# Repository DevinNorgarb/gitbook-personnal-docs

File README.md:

# Personal documentation

Public knowledge base at **[devinn.org](https://devinn.org)** — notes on software engineering, embedded systems, robotics, GIS, and related topics.

## Site vs repository

| File | Purpose |
|------|---------|
| [`index.md`](index.md)
| `README.md` | This file — GitHub repo overview and contributor setup |

Do not sync `README.md` over `index.md`; they serve different audiences.

## Contributing

See [CONTRIBUTING.md](CONTRIBUTING.md) for how to add or edit pages.

## Style guide

See [.github/DOCUMENTATION-STYLE-GUIDE.md](.github/DOCUMENTATION-STYLE-GUIDE.md) for documentation conventions.

## Local development

- **Prerequisites**: [Node.js](https://nodejs.org/) 20+ and `npm ci`.
- **Local preview**: `npm run docs:dev` — runs `docs:prep` then starts VitePress (default port **5173**).
- **Production build**: `npm run docs:prep && npm run docs:build` locally, or rely on CI (prep then build). Output: [`.vitepress/dist/`](.vitepress/dist/) (gitignored).

## Publishing (GitHub Pages)

Pushes to `main` or `master` run [`.github/workflows/vitepress.yml`](.github/workflows/vitepress.yml), which deploys **`.vitepress/dist`** to the **`gh-pages`** branch. Primary URL: [https://docs.f1y.ing/](https://docs.f1y.ing/).

**Audit reports**: `npm run docs:audit` writes `docs-audit-report.json` and `docs-audit-report.md` (gitignored). Configure thresholds in [`audit.config.json`](audit.config.json).

GitBook-only constructs in markdown were converted for portable rendering; see [`scripts/archive/`](scripts/archive/) for archived migration tooling.

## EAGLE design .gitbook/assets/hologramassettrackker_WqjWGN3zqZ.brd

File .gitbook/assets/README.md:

# Overview    

> "Think globally, `act` locally"

Run your [GitHub Actions](https://developer.github.com/actions/) locally! Why would you want to do this? Two reasons:

- **Fast Feedback** - Rather than having to commit/push every time you want to test out the changes you are making to your `.github/workflows/` files (or for any changes to embedded GitHub actions), you can use `act` to run the actions locally. The [environment variables](https://help.github.com/en/actions/configuring-and-managing-workflows/using-environment-variables#default-environment-variables) and [filesystem](https://help.github.com/en/actions/reference/virtual-environments-for-github-hosted-runners#filesystems-on-github-hosted-runners) are all configured to match what GitHub provides.
- **Local Task Runner** - I love [make](<https://en.wikipedia.org/wiki/Make_(software)>). However, I also hate repeating myself. With `act`, you can use the GitHub Actions defined in your `.github/workflows/` to replace your `Makefile`!

## How Does It Work?

When you run `act` it reads in your GitHub Actions from `.github/workflows/` and determines the set of actions that need to be run. It uses the Docker API to either pull or build the necessary images, as defined in your workflow files and finally determines the execution path based on the dependencies that were defined. Once it has the execution path, it then uses the Docker API to run containers for each action based on the images prepared earlier. The [environment variables](https://help.github.com/en/actions/configuring-and-managing-workflows/using-environment-variables#default-environment-variables) and [filesystem](https://docs.github.com/en/actions/using-github-hosted-runners/about-github-hosted-runners#file-systems) are all configured to match what GitHub provides.

Let's see it in action with a [sample repo](https://github.com/cplee/github-actions-demo)!

## Act User Guide

Please look at the [act user guide](https://nektosact.com) for more documentation.

## Installation

## Necessary prerequisites for running `act`

`act` depends on `docker` to run workflows.

If you are using macOS, please be sure to follow the steps outlined in [Docker Docs for how to install Docker Desktop for Mac](https://docs.docker.com/docker-for-mac/install/).

If you are using Windows, please follow steps for [installing Docker Desktop on Windows](https://docs.docker.com/docker-for-windows/install/).

If you are using Linux, you will need to [install Docker Engine](https://docs.docker.com/engine/install/).

`act` is currently not supported with `podman` or other container backends (it might work, but it's not guaranteed). Please see [#303](https://github.com/nektos/act/issues/303) for updates.

## Installation through package managers

### [Homebrew](https://brew.sh/) (Linux/macOS)

```shell
brew install act
```json

or if you want to install version based on latest commit, you can run below (it requires compiler to be installed but Homebrew will suggest you how to install it, if you don't have it):

```shell
brew install act --HEAD
```json

### [MacPorts](https://www.macports.org) (macOS)

```shell
sudo port install act
```json

### [Chocolatey](https://chocolatey.org/) (Windows)

```shell
choco install act-cli
```json

### [Scoop](https://scoop.sh/) (Windows)

```shell
scoop install act
```json

### [Winget](https://learn.microsoft.com/en-us/windows/package-manager/) (Windows)

```shell
winget install nektos.act
```json

### [AUR](https://aur.archlinux.org/packages/act/) (Linux)

```shell
yay -Syu act
```json

### [COPR](https://copr.fedorainfracloud.org/coprs/rubemlrm/act-cli/) (Linux)

```shell
dnf copr enable rubemlrm/act-cli
dnf install act-cli
```json

### [Nix](https://nixos.org) (Linux/macOS)

[Nix recipe](https://github.com/NixOS/nixpkgs/blob/master/pkgs/development/tools/misc/act/default.nix)

Global install:

```sh
nix-env -iA nixpkgs.act
```bash

or through `nix-shell`:

```sh
nix-shell -p act
```bash

Using the latest [Nix command](https://nixos.wiki/wiki/Nix_command), you can run directly :

```sh
nix run nixpkgs#act
```bash

## Installation as GitHub CLI extension

Act can be installed as a [GitHub CLI](https://cli.github.com/) extension:

```sh
gh extension install https://github.com/nektos/gh-act
```bash

## Other install options

### Bash script

Run this command in your terminal:

```shell
curl -s https://raw.githubusercontent.com/nektos/act/master/install.sh | sudo bash
```bash

### Manual download

Download the [latest release](https://github.com/nektos/act/releases/latest) and add the path to your binary into your PATH.

## Example commands

```sh
## Command structure:
act [<event>] [options]
If no event name passed, will default to "on: push"
If actions handles only one event it will be used as default instead of "on: push"

## List all actions for all events:
act -l

## List the actions for a specific event:
act workflow_dispatch -l

## List the actions for a specific job:
act -j test -l

## Run the default (`push`) event:
act

## Run a specific event:
act pull_request

## Run a specific job:
act -j test

## Collect artifacts to the /tmp/artifacts folder:
act --artifact-server-path /tmp/artifacts

## Run a job in a specific workflow (useful if you have duplicate job names)
act -j lint -W .github/workflows/checks.yml

## Run in dry-run mode:
act -n

## Enable verbose-logging (can be used with any of the above commands)
act -v
```bash

## First `act` run

When running `act` for the first time, it will ask you to choose image to be used as default.
It will save that information to `~/.actrc`, please refer to [Configuration](#configuration) for more information about `.actrc` and to [Runners](#runners) for information about used/available Docker images.

## `GITHUB_TOKEN`

GitHub [automatically provides](https://docs.github.com/en/actions/security-guides/automatic-token-authentication#about-the-github_token-secret) a `GITHUB_TOKEN` secret when running workflows inside GitHub.

If your workflow depends on this token, you need to create a [personal access token](https://docs.github.com/en/authentication/keeping-your-account-and-data-secure/creating-a-personal-access-token) and pass it to `act` as a secret:

```bash
act -s GITHUB_TOKEN=[insert token or leave blank and omit equals for secure input]
```bash

If [GitHub CLI](https://cli.github.com/) is installed, the [`gh auth token`](https://cli.github.com/manual/gh_auth_token) command can be used to automatically pass the token to act

```bash
act -s GITHUB_TOKEN="$(gh auth token)"
```php

**WARNING**: `GITHUB_TOKEN` will be logged in shell history if not inserted through secure input or (depending on your shell config) the command is prefixed with a whitespace.

## Known Issues

## Services

Services are not currently supported but are being worked on. See: [#173](https://github.com/nektos/act/issues/173)

## `MODULE_NOT_FOUND`

A `MODULE_NOT_FOUND` during `docker cp` command [#228](https://github.com/nektos/act/issues/228) can happen if you are relying on local changes that have not been pushed. This can get triggered if the action is using a path, like:

```yaml
- name: test action locally
  uses: ./
```php

In this case, you _must_ use `actions/checkout@v2` with a path that _has the same name as your repository_. If your repository is called _my-action_, then your checkout step would look like:

```yaml
steps:
  - name: Checkout
    uses: actions/checkout@v2
    with:
      path: "my-action"
```javascript

If the `path:` value doesn't match the name of the repository, a `MODULE_NOT_FOUND` will be thrown.

## `docker context` support

The current `docker context` isn't respected ([#583](https://github.com/nektos/act/issues/583)).

You can work around this by setting `DOCKER_HOST` before running `act`, with e.g:

```bash
export DOCKER_HOST=$(docker context inspect --format '{{.Endpoints.docker.Host}}')
```bash

## Runners

GitHub Actions offers managed [virtual environments](https://help.github.com/en/actions/reference/virtual-environments-for-github-hosted-runners) for running workflows. In order for `act` to run your workflows locally, it must run a container for the runner defined in your workflow file. Here are the images that `act` uses for each runner type and size:

| GitHub Runner   | Micro Docker Image               | Medium Docker Image                               | Large Docker Image                                 |
| --------------- | -------------------------------- | ------------------------------------------------- | -------------------------------------------------- |
| `ubuntu-latest` | [`node:16-buster-slim`][micro]   | [`catthehacker/ubuntu:act-latest`][docker_images] | [`catthehacker/ubuntu:full-latest`][docker_images] |
| `ubuntu-22.04`  | [`node:16-bullseye-slim`][micro] | [`catthehacker/ubuntu:act-22.04`][docker_images]  | `unavailable`                                      |
| `ubuntu-20.04`  | [`node:16-buster-slim`][micro]   | [`catthehacker/ubuntu:act-20.04`][docker_images]  | [`catthehacker/ubuntu:full-20.04`][docker_images]  |
| `ubuntu-18.04`  | [`node:16-buster-slim`][micro]   | [`catthehacker/ubuntu:act-18.04`][docker_images]  | [`catthehacker/ubuntu:full-18.04`][docker_images]  |

[micro]: https://hub.docker.com/_/buildpack-deps
[docker_images]: https://github.com/catthehacker/docker_images

Windows and macOS based platforms are currently **unsupported and won't work** (see issue [#97](https://github.com/nektos/act/issues/97))

## Please see [IMAGES.md](./IMAGES.md) for more information about the Docker images that can be used with `act`

## Default runners are intentionally incomplete

These default images do **not** contain **all** the tools that GitHub Actions offers by default in their runners.
Many things can work improperly or not at all while running those image.
Additionally, some software might still not work even if installed properly, since GitHub Actions are running in fully virtualized machines while `act` is using Docker containers (e.g. Docker does not support running `systemd`).
In case of any problems [please create issue](https://github.com/nektos/act/issues/new/choose) in respective repository (issues with `act` in this repository, issues with `nektos/act-environments-ubuntu:18.04` in [`nektos/act-environments`](https://github.com/nektos/act-environments) and issues with any image from user `catthehacker` in [`catthehacker/docker_images`](https://github.com/catthehacker/docker_images))

## Alternative runner images

If you need an environment that works just like the corresponding GitHub runner then consider using an image provided by [nektos/act-environments](https://github.com/nektos/act-environments):

- [`nektos/act-environments-ubuntu:18.04`](https://hub.docker.com/r/nektos/act-environments-ubuntu/tags) - built from the Packer file GitHub uses in [actions/virtual-environments](https://github.com/actions/runner).

:warning: :elephant: `*** WARNING - this image is >18GB 😱***`

- [`catthehacker/ubuntu:full-*`](https://github.com/catthehacker/docker_images/pkgs/container/ubuntu) - built from Packer template provided by GitHub, see [catthehacker/virtual-environments-fork](https://github.com/catthehacker/virtual-environments-fork) or [catthehacker/docker_images](https://github.com/catthehacker/docker_images) for more information

## Using local runner images

The `--pull` flag is set to true by default due to a breaking on older default docker images. This would pull the docker image everytime act is executed.

Set `--pull` to false if a local docker image is needed
```sh
  act --pull=false
```php

## Use an alternative runner image

To use a different image for the runner, use the `-P` option.

```sh
act -P <platform>=<docker-image>
```php

If your workflow uses `ubuntu-18.04`, consider below line as an example for changing Docker image used to run that workflow:

```sh
act -P ubuntu-18.04=nektos/act-environments-ubuntu:18.04
```php

If you use multiple platforms in your workflow, you have to specify them to change which image is used.
For example, if your workflow uses `ubuntu-18.04`, `ubuntu-16.04` and `ubuntu-latest`, specify all platforms like below

```sh
act -P ubuntu-18.04=nektos/act-environments-ubuntu:18.04 -P ubuntu-latest=ubuntu:latest -P ubuntu-16.04=node:16-buster-slim
```php

## Secrets

To run `act` with secrets, you can enter them interactively, supply them as environment variables or load them from a file. The following options are available for providing secrets:

- `act -s MY_SECRET=somevalue` - use `somevalue` as the value for `MY_SECRET`.
- `act -s MY_SECRET` - check for an environment variable named `MY_SECRET` and use it if it exists. If the environment variable is not defined, prompt the user for a value.
- `act --secret-file my.secrets` - load secrets values from `my.secrets` file.
  - secrets file format is the same as `.env` format

## Vars

To run `act` with repository variables that are acessible inside the workflow via ${{ vars.VARIABLE }}, you can enter them interactively or load them from a file. The following options are available for providing github repository variables:

- `act --var VARIABLE=somevalue` - use `somevalue` as the value for `VARIABLE`.
- `act --var-file my.variables` - load variables values from `my.variables` file.
  - variables file format is the same as `.env` format

## Configuration

You can provide default configuration flags to `act` by either creating a `./.actrc` or a `~/.actrc` file. Any flags in the files will be applied before any flags provided directly on the command line. For example, a file like below will always use the `nektos/act-environments-ubuntu:18.04` image for the `ubuntu-latest` runner:

```sh
## sample .actrc file
-P ubuntu-latest=nektos/act-environments-ubuntu:18.04
```php

Additionally, act supports loading environment variables from an `.env` file. The default is to look in the working directory for the file but can be overridden by:

```sh
act --env-file my.env
```php

`.env`:

```env
MY_ENV_VAR=MY_ENV_VAR_VALUE
MY_2ND_ENV_VAR="my 2nd env var value"
```php

## Skipping jobs

You cannot use the `env` context in job level if conditions, but you can add a custom event property to the `github` context. You can use this method also on step level if conditions.

```yml
on: push
jobs:
  deploy:
    if: ${{ !github.event.act }} # skip during local actions testing
    runs-on: ubuntu-latest
    steps:
    - run: exit 0
```php

And use this `event.json` file with act otherwise the Job will run:

```json
{
    "act": true
}
```php

Run act like

```sh
act -e event.json
```php

_Hint: you can add / append `-e event.json` as a line into `./.actrc`_

## Skipping steps

Act adds a special environment variable `ACT` that can be used to skip a step that you
don't want to run locally. E.g. a step that posts a Slack message or bumps a version number.
**You cannot use this method in job level if conditions, see [Skipping jobs](#skipping-jobs)**

```yml
- name: Some step
  if: ${{ !env.ACT }}
  run: |
    ...
```json

## Events

Every [GitHub event](https://developer.github.com/v3/activity/events/types) is accompanied by a payload. You can provide these events in JSON format with the `--eventpath` to simulate specific GitHub events kicking off an action. For example:

```json
{
  "pull_request": {
    "head": {
      "ref": "sample-head-ref"
    },
    "base": {
      "ref": "sample-base-ref"
    }
  }
}
```bash

```sh
act pull_request -e pull-request.json
```bash

Act will properly provide `github.head_ref` and `github.base_ref` to the action as expected.

## Pass Inputs to Manually Triggered Workflows

Example workflow file

```yaml
on:
  workflow_dispatch:
    inputs:
      NAME:
        description: "A random input name for the workflow"
        type: string
      SOME_VALUE:
        description: "Some other input to pass"
        type: string

jobs:
  test:
    name: Test
    runs-on: ubuntu-latest

    steps:
      - name: Test with inputs
        run: |
          echo "Hello ${{ github.event.inputs.NAME }} and ${{ github.event.inputs.SOME_VALUE }}!"
```php

## via input or input-file flag

- `act --input NAME=somevalue` - use `somevalue` as the value for `NAME` input.
- `act --input-file my.input` - load input values from `my.input` file.
  - input file format is the same as `.env` format

## via JSON

Example JSON payload file conveniently named `payload.json`

```json
{
  "inputs": {
    "NAME": "Manual Workflow",
    "SOME_VALUE": "ABC"
  }
}
```php

Command for triggering the workflow

```sh
act workflow_dispatch -e payload.json
```php

## GitHub Enterprise

Act supports using and authenticating against private GitHub Enterprise servers.
To use your custom GHE server, set the CLI flag `--github-instance` to your hostname (e.g. `github.company.com`).

Please note that if your GHE server requires authentication, we will use the secret provided via `GITHUB_TOKEN`.

Please also see the [official documentation for GitHub actions on GHE](https://docs.github.com/en/enterprise-server@3.0/admin/github-actions/about-using-actions-in-your-enterprise) for more information on how to use actions.

## Support

Need help? Ask on [Gitter](https://gitter.im/nektos/act)!

## Contributing

Want to contribute to act? Awesome! Check out the [contributing guidelines](CONTRIBUTING.md) to get involved.

## Manually building from source

- Install Go tools 1.20+ - (<https://golang.org/doc/install>)
- Clone this repo `git clone git@github.com:nektos/act.git`
- Run unit tests with `make test`
- Build and install: `make install`

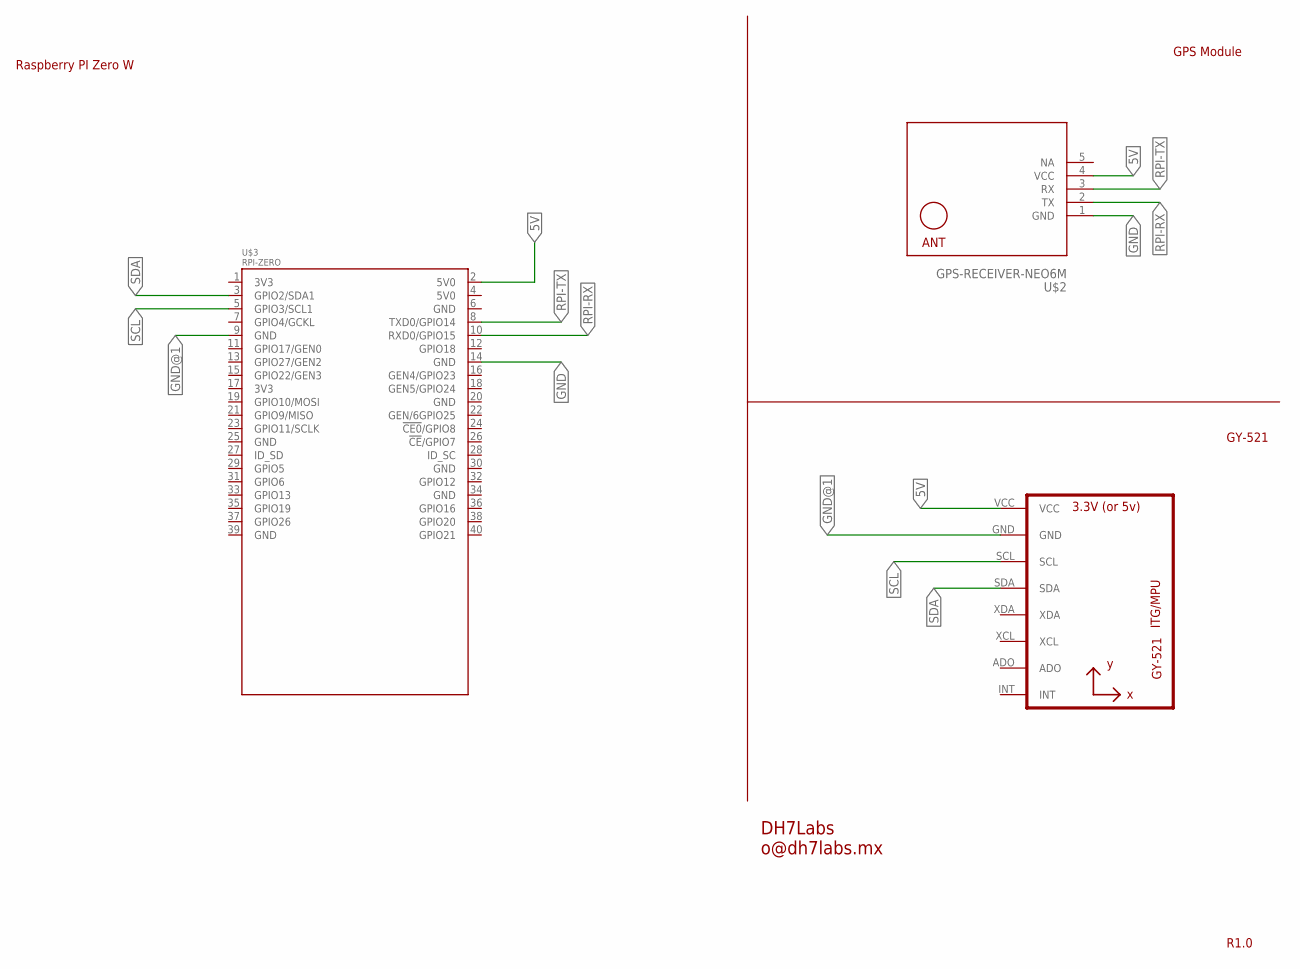
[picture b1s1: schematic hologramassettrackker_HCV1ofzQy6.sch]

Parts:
U1: GY-521MPU6050; GY-521
U$2: GPS-RECEIVER-NEO6M
U$3: RPI-ZERO; RASP_PI_ZERO_BOARD_FULL

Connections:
5V: U1.VCC, U$2.4 (VCC), U$3.2 (5V0)
GND: U$2.1 (GND), U$3.14 (GND)
GND@1: U1.GND, U$3.9 (GND)
RPI-RX: U$2.2 (TX), U$3.10 (RXD0/GPIO15)
RPI-TX: U$2.3 (RX), U$3.8 (TXD0/GPIO14)
SCL: U1.SCL, U$3.5 (GPIO3/SCL1)
SDA: U1.SDA, U$3.3 (GPIO2/SDA1)

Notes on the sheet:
R1.0
DH7Labs o@dh7labs.mx
GPS Module
Raspberry PI Zero W
GY-521

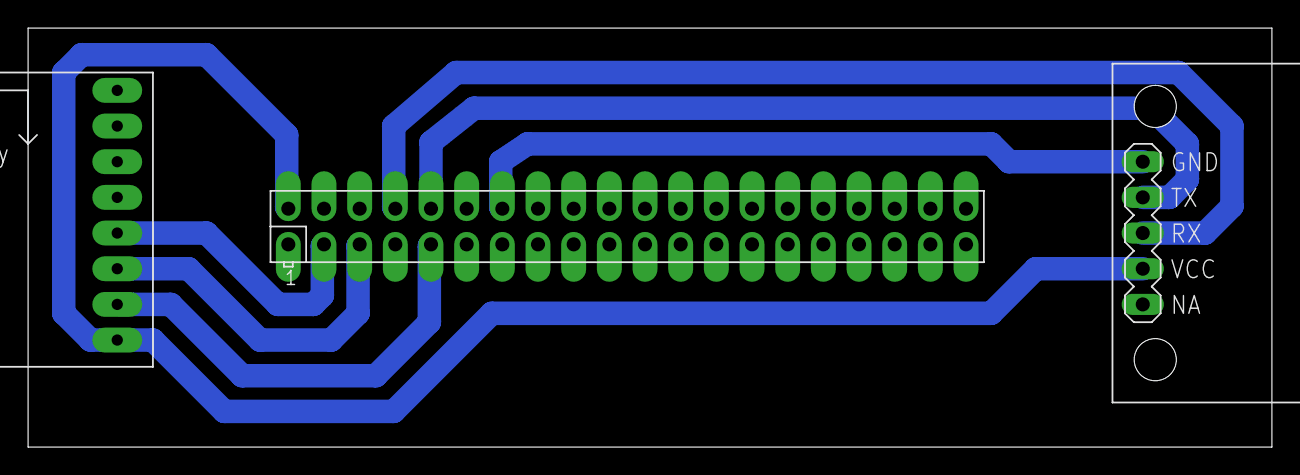
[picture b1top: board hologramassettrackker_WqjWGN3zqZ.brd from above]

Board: 2 copper layers, 88.6 x 29.8 mm, 3 parts (0 on the bottom side), 7 nets.

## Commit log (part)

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2022-06-17 GitBook: [#68] No subject
2022-06-19 GitBook: [#72] No subject
2022-06-23 GitBook: [#79] No subject
2022-06-27 GitBook: [#84] No subject
2022-07-06 GitBook: [#88] No subject
2022-07-16 GitBook: [#92] No subject
2022-07-23 GitBook: [#96] No subject
2022-07-29 GitBook: [#103] No subject
2022-09-30 GitBook: [#109] No subject
2022-10-27 GitBook: [#114] No subject
2022-11-19 GitBook: [#118] No subject
2022-12-21 GitBook: [#121] No subject
2023-01-01 GitBook: [#125] No subject
2023-03-12 GITBOOK-132: No subject
2023-03-17 GITBOOK-135: No subject
2023-03-22 GITBOOK-143: No subject
2023-03-30 GITBOOK-146: Devin's Mar 30 changes
2023-04-05 GITBOOK-150: change request with no subject merged in GitBook
2023-04-06 GITBOOK-153: Devin's Apr 7 changes
2023-04-16 GITBOOK-161: Devin's Apr 16 changes
2023-04-28 GITBOOK-164: Devin's Apr 28 changes
2023-04-28 GITBOOK-168: Devin's Apr 28 changes
2023-04-29 GITBOOK-173: Devin's Apr 29 changes
2023-04-29 GITBOOK-178: change request with no subject merged in GitBook
2023-04-29 GITBOOK-180: change request with no subject merged in GitBook
2023-04-30 GITBOOK-184: change request with no subject merged in GitBook
2023-05-01 GITBOOK-187: change request with no subject merged in GitBook
2023-05-10 GITBOOK-191: change request with no subject merged in GitBook
2023-05-10 GITBOOK-196: change request with no subject merged in GitBook
2023-05-20 GITBOOK-203: change request with no subject merged in GitBook
2023-05-24 GITBOOK-208: change request with no subject merged in GitBook
2023-05-28 GITBOOK-212: change request with no subject merged in GitBook
2023-05-31 GITBOOK-217: change request with no subject merged in GitBook
2023-06-01 GITBOOK-224: change request with no subject merged in GitBook
2023-06-01 GITBOOK-227: change request with no subject merged in GitBook
2023-06-03 GITBOOK-232: change request with no subject merged in GitBook
2023-06-03 GITBOOK-235: change request with no subject merged in GitBook
2023-06-04 GITBOOK-238: change request with no subject merged in GitBook
2023-06-05 GITBOOK-242: Devin's Jun 5 changes
2023-06-10 GITBOOK-246: Devin's Jun 6 changes
2023-06-26 GITBOOK-249: Devin's Jun 26 changes
2023-06-30 GITBOOK-254: Devin's Jun 30 changes
2023-07-26 GITBOOK-258: change request with no subject merged in GitBook
2023-08-12 GITBOOK-257: Devin's Jun 30 changes
2023-09-25 GITBOOK-266: change request with no subject merged in GitBook
2023-09-25 GITBOOK-269: change request with no subject merged in GitBook
2023-09-30 GITBOOK-272: change request with no subject merged in GitBook
2023-10-13 GITBOOK-276: change request with no subject merged in GitBook
2023-10-16 GITBOOK-279: change request with no subject merged in GitBook
2023-10-17 GITBOOK-282: change request with no subject merged in GitBook
2023-10-23 GITBOOK-286: change request with no subject merged in GitBook
2023-10-23 GITBOOK-289: change request with no subject merged in GitBook
2023-10-23 GITBOOK-292: change request with no subject merged in GitBook
2023-10-24 GITBOOK-296: change request with no subject merged in GitBook
2023-10-28 GITBOOK-300: change request with no subject merged in GitBook
2023-10-29 GITBOOK-303: change request with no subject merged in GitBook
2023-11-02 GITBOOK-306: change request with no subject merged in GitBook
2023-12-07 GITBOOK-310: change request with no subject merged in GitBook
2023-12-15 GITBOOK-313: change request with no subject merged in GitBook
2023-12-15 GITBOOK-316: change request with no subject merged in GitBook
2023-12-22 GITBOOK-320: change request with no subject merged in GitBook
2023-12-27 GITBOOK-323: change request with no subject merged in GitBook
2023-12-30 GITBOOK-327: change request with no subject merged in GitBook
2024-01-20 GITBOOK-333: change request with no subject merged in GitBook
2024-01-28 GITBOOK-338: change request with no subject merged in GitBook
2024-02-08 GITBOOK-341: change request with no subject merged in GitBook
2024-02-14 GITBOOK-345: change request with no subject merged in GitBook
2024-02-22 GITBOOK-349: change request with no subject merged in GitBook
2024-02-29 GITBOOK-351: change request with no subject merged in GitBook
2024-03-19 GITBOOK-355: change request with no subject merged in GitBook
2024-04-10 GITBOOK-361: change request with no subject merged in GitBook
2024-04-11 GITBOOK-364: change request with no subject merged in GitBook
2024-06-17 GITBOOK-368: change request with no subject merged in GitBook
2024-08-28 GITBOOK-371: Devin's Aug 28 changes
2025-01-08 GITBOOK-374: change request with no subject merged in GitBook
2025-01-08 GITBOOK-378: change request with no subject merged in GitBook
2025-01-15 GITBOOK-381: change request with no subject merged in GitBook
2026-02-18 Correct typos and improve formatting in multiple markdown files. Changes include consistent naming of "VirtualBox," clarification of CORS definitions, and adjustments to installation commands for Doc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
2026-02-18 Enhance README files for Poetry and Pyenv with comprehensive installation and usage instructions. Improve formatting, clarity, and consistency throughout the documentation, including detailed guideli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
2026-02-18 GITBOOK-383: change request with no subject merged in GitBook
2026-03-01 Enhance README files for Poetry and Pyenv with comprehensive installation and usage instructions. Significant improvements include detailed guidelines for setting up environments, managing Python ver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
2026-03-02 Add markdown repository refactor plan for standardization and improvement
    - Introduced a new plan for sequentially refactoring all Markdown files in the repository, focusing on fixing heading hierarchy, spacing, code fences, list formatting, and relative links.
    - Established a checklist for required fixes per file to ensure consistency and completeness without altering meaningful content or file structure.
    - Outlined the scope, constraints, and execution flow for the refactor process, emphasizing the importance of maintaining original file names and locations.
    - Included recommendations for processing order and handling edge cases to streamline the refactoring effort.
2026-04-15 Refactor documentation plans to improve clarity and formatting
    - Added a blank line for better readability in the documentation refactoring plan.
    - Standardized formatting in the markdown repository refactor plan by removing unnecessary line breaks, enhancing overall structure and consistency.
2026-04-15 Update SUMMARY.md and continual-learning.json for consistency and tracking
    - Removed redundant README links from the Python libraries section in SUMMARY.md for improved clarity.
    - Updated the `turnsSinceLastRun` value and `lastProcessedGenerationId` in continual-learning.json to reflect the latest state changes.
2026-04-15 Transition documentation from mdBook to VitePress
    - Removed `book.toml` and associated mdBook configurations to fully adopt VitePress for documentation.
    - Updated `.gitignore` to exclude VitePress build artifacts and added necessary directories.
    - Revised `README.md`, `CONTRIBUTING.md`, and `.github/DOCUMENTATION-STYLE-GUIDE.md` to reflect the new VitePress setup and usage instructions.
    - Introduced new scripts for generating the sidebar and auditing documentation quality.
    - Added GitHub Actions workflow for VitePress deployment and documentation auditing.
    - Created initial VitePress configuration and sidebar structure based on existing documentation hierarchy.
2026-04-20 docs(import): add Android Runtime Dalvik/ART notes
    Import and structure ProAndroidDev's Android Runtime article and index it under Android App Development for easier discovery.
    Made-with: Cursor
2026-04-21 docs(import): add DUMLdore fork and RM500 privilege escalation notes
    Document DevinNorgarb/DUMLdore README and icanhack RM500 djilink Binder LPE; link both from SUMMARY under pen-testing drones.
    Made-with: Cursor
2026-04-23 fix(ci): skip external URLs in lychee check
    Exclude http(s) links from markdown link checks so transient third-party TLS and rate-limit issues do not fail CI.
2026-04-23 fix(docs): normalize unsupported code fence languages
    Replace unsupported markdown fence language tags with supported ones to reduce VitePress highlight fallback warnings during builds.
2026-04-23 fix(docs): resolve sidebar section landing page 404s
    Map section README entries to `/path/README` links when cleanUrls is disabled so sidebar parent pages open valid landing documents instead of 404 routes.
2026-05-10 docs(import): add Sonoff RFR3 433 MQTT gateway mod notes
2026-05-21 docs(import): Last Minute Engineers nRF24L01 Arduino wireless guide
    Add structured notes with eighteen mirrored tutorial figures covering
    variants, RF24 wiring, multicast, bidirectional demos, and 5 V adapters.
2026-06-06 docs(arch): add architecture review tracking document
    Capture deepening opportunities from the codebase architecture review
    so each item can be tackled on its own branch and PR.
2026-06-06 docs(runbook): consolidate Docker-without-sudo into canonical page
    Point variant nav entries at one canonical runbook, merge Ubuntu and
    Docker Desktop notes there, and remove the orphan duplicate via git.
2026-06-06 docs(arch): fix item 4 PR link
2026-06-06 feat(monitoring): add Sentry Vue SDK to VitePress site
    Wire self-hosted Sentry for error monitoring, tracing, replay, and logs
    in production builds via a custom theme extension and CI secret.
2026-06-06 docs(arch): fix item 3 PR link
2026-06-10 feat(docs): section indexes, topic dedupe, and nav hiding
    Generate "In this section" blocks from SUMMARY.md with YAML-safe blurbs,
    canonical topic routing via topic-canonical.json, and nav.hidden.json to
    exclude duplicate DJI/tutorial stubs from the VitePress build.
2026-06-10 docs: add UART, I2C, and SPI protocol reference pages
    Match the practical style of the existing serial tutorial with wiring
    notes, Arduino examples, common mistakes, and cross-links in robotics.
2026-06-11 chore(docs): regenerate VitePress sidebar after rebase onto main
    Include both It's FOSS and Pi My Life Up Proxmox entries so docs:check-sidebar passes.
2026-06-12 Import content into 12 stub pages (batch 1).
    Enrich OBD2, pen-testing, ESP32, magnetico, and scrapers stubs with structured summaries and preserved source links; add batch tracker for the remaining import loop.
2026-06-12 Import stub page content (batch 4).
    Enrich software engineering docs for Obsidian, n8n, Capacitor, ML Kit, OpenMV, frontend indexes, Freqtrade, and k3s; advance batch tracker to 5.
2026-06-12 deploy: 5f119bb196b2683a1654e99d8ed6a94ae6f97b10
2026-06-19 docs(import): add Google Play apps and home page Apps section
    Import GPS Remote and SoFly Play Store listings, add sleek app cards on the VitePress home page, and run docs CI on the self-hosted runner.
2026-06-20 fix(ci): repair stub-import frontmatter and home app icons for VitePress build
    Replace malformed YAML descriptions from stub imports so docs:build succeeds, and load Play Store icons via CSS backgrounds to avoid Rollup resolution errors on the home page.
2026-06-23 docs(import): add Concox GT710 firmware extraction notes
    UART metadata extraction, PCB photos, and macOS paths for a full GT710
    firmware clone (mtkclient, Black Magic Probe, NT71 GPS board).
2026-06-24 fix(docs): restore home app icons and unblock VitePress build
    Move Play Store icons into root public/ so they deploy with the site, and point Repomix’s sponsor badge at the upstream SVG so Rollup no longer fails on a missing local path.
2026-06-25 docs(import): compress harness engineering diagrams to 1200px WebP
    Downscale from full Medium CDN resolution (~19 MB PNG) to doc-sized WebP assets (~1.2 MB total) while keeping diagrams readable in VitePress.

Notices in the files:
parts and their libraries:
diy-modules: Released under the Creative Commons Attribution 4.0 International License: http://creativecommons.org/licenses/by/4.0
